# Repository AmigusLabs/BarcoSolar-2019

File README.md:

# BarcoSolar-2019
Barco solar Regata Marine Instruments 2019

Ver proyecto en [Amigus Labs](http://www.amiguslabs.org/portfolio_page/amigus-labs-barco-solar19/)

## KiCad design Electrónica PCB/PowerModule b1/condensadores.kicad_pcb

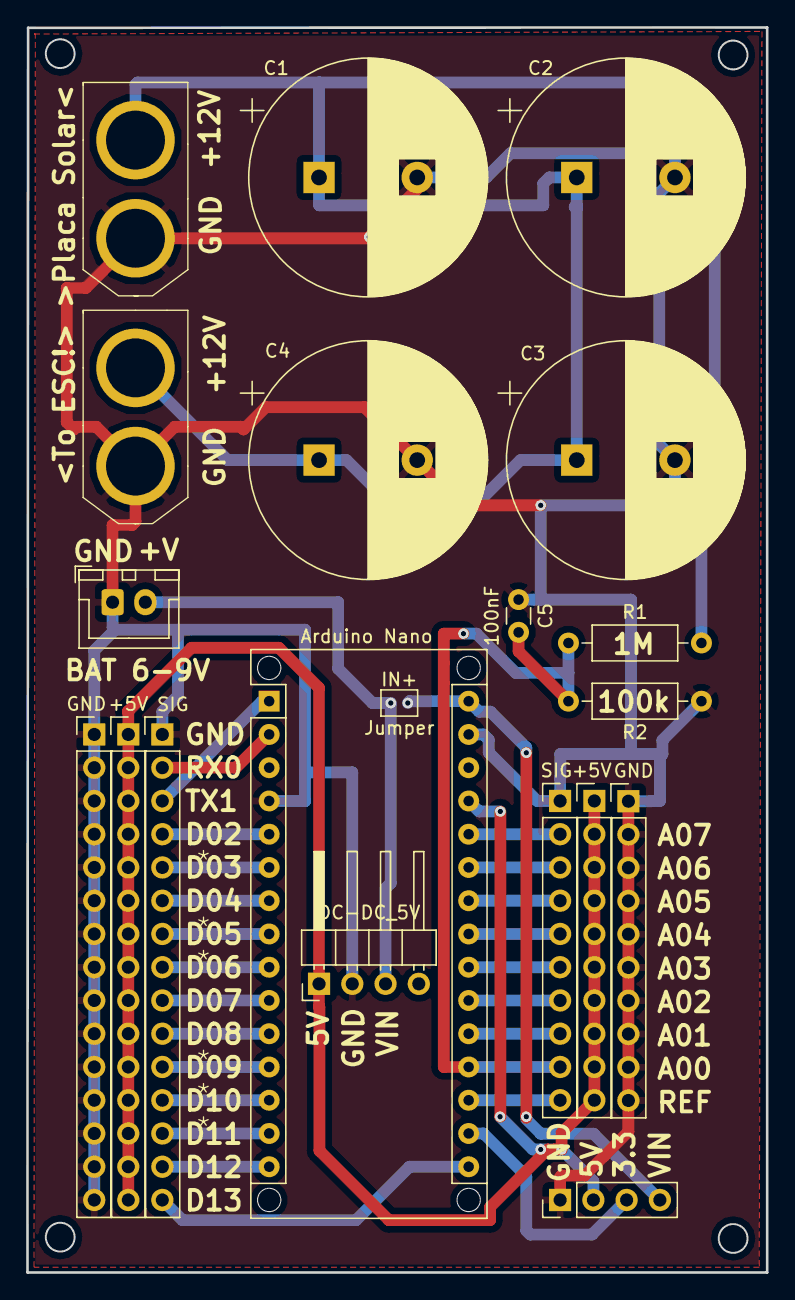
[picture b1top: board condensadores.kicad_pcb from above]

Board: 2 copper layers, 56.5 x 95.1 mm, 20 parts (0 on the bottom side), 28 nets.

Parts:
+5V: +5V; PinHeader_1x15_P2.54mm_Vertical
+5V#2: +5V; PinHeader_1x10_P2.54mm_Vertical
Arduino Nano: Arduino_Nano_v3.x; Arduino_Nano_WithMountingHoles
C1, C2, C3, C4: 35V4700uF; CP_Radial_D18.0mm_P7.50mm
C5: 100nF; C_Disc_D3.0mm_W1.6mm_P2.50mm
DC-DC_5V: DC-DC; PinHeader_1x04_P2.54mm_Horizontal
GND: GND; PinHeader_1x15_P2.54mm_Vertical
GND#2: GND; PinHeader_1x10_P2.54mm_Vertical
IN+: Jumper; SolderJumper-2_P1.3mm_Open_Pad1.0x1.5mm
J1, J1#2: Placa Solar +12V; XT60
J3: BAT 6-9V; JST_XH_B02B-XH-A_1x02_P2.50mm_Vertical
JA3: SIG 3; PinHeader_1x04_P2.54mm_Vertical
R1: 1M; R_Axial_DIN0207_L6.3mm_D2.5mm_P10.16mm_Horizontal
R2: 100K; R_Axial_DIN0207_L6.3mm_D2.5mm_P10.16mm_Horizontal
SIG: SIG; PinHeader_1x15_P2.54mm_Vertical
SIG#2: SIG; PinHeader_1x10_P2.54mm_Vertical

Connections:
+5V: +5V.1, +5V.2, +5V.3, +5V.4, +5V.5, +5V.6, +5V.7, +5V.8, +5V.9, +5V.10, +5V.11, +5V.12, +5V.13, +5V.14, +5V.15, +5V#2.1, +5V#2.2, +5V#2.3, +5V#2.4, +5V#2.5, +5V#2.6, +5V#2.7, +5V#2.8, +5V#2.9, +5V#2.10, Arduino Nano.27, DC-DC_5V.1, JA3.2
/+12V: C1.1, C2.1, C3.1, C4.1, J1.2, J1#2.2, R1.2
A0: Arduino Nano.19, C5.2, R1.1, R2.2, SIG#2.9
GND: Arduino Nano.4, Arduino Nano.29, C1.2, C2.2, C3.2, C4.2, C5.1, DC-DC_5V.2, GND.1, GND.2, GND.3, GND.4, GND.5, GND.6, GND.7, GND.8, GND.9, GND.10, GND.11, GND.12, GND.13, GND.14, GND.15, GND#2.1, GND#2.2, GND#2.3, GND#2.4, GND#2.5, GND#2.6, GND#2.7, GND#2.8, GND#2.9, GND#2.10, J1.1, J1#2.1, J3.1, JA3.1, R2.1, SIG.1, SIG#2.1
IN+: Arduino Nano.30, DC-DC_5V.3, IN+.1, IN+.2, J3.2, JA3.4
unnamed: Arduino Nano.1, SIG.3
unnamed: Arduino Nano.2, SIG.2
unnamed: Arduino Nano.5, SIG.4
unnamed: Arduino Nano.6, SIG.5
unnamed: Arduino Nano.7, SIG.6
unnamed: Arduino Nano.8, SIG.7
unnamed: Arduino Nano.9, SIG.8
unnamed: Arduino Nano.10, SIG.9
unnamed: Arduino Nano.11, SIG.10
unnamed: Arduino Nano.12, SIG.11
unnamed: Arduino Nano.13, SIG.12
unnamed: Arduino Nano.14, SIG.13
unnamed: Arduino Nano.15, SIG.14
unnamed: Arduino Nano.16, SIG.15
unnamed: Arduino Nano.17, JA3.3
unnamed: Arduino Nano.18, SIG#2.10
unnamed: Arduino Nano.20, SIG#2.8
unnamed: Arduino Nano.21, SIG#2.7
unnamed: Arduino Nano.22, SIG#2.6
unnamed: Arduino Nano.23, SIG#2.5
unnamed: Arduino Nano.24, SIG#2.4
unnamed: Arduino Nano.25, SIG#2.3
unnamed: Arduino Nano.26, SIG#2.2

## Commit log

2019-10-26 ficheros
2020-02-28 Añadida url al proyecto en Amigus Labs
